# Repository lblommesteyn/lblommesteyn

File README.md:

### Hi there 👋

Welcome to My GitHub Profile! I'm glad you stopped by, my name is Luke Blommesteyn and I'm a software engineer. If you've never met me before here's some information about me:

- 🌱 I’m currently reading about the distributed systems, poker, and computer vision!
- 📫 How to reach me: lukeblommesteyn[at]gmail.com

Learn more about me [here](https://lukeblom.vercel.app)

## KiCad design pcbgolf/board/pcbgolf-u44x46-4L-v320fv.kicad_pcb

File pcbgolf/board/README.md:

# Generated boards

| file | board | layers | status |
|---|---|---|---|
| `pcbgolf-stock-2L.kicad_pcb` | 42.65 x 46.65 mm | 2 | placed + netlisted, **not routed** |

## How it is built

`tools/mkboard.py` does not synthesise footprints. It loads the upstream
`pcbgolf.kicad_pcb` — a known-valid KiCad 10 file — keeps every footprint block
verbatim, and changes only:

* the footprint's position, rotation and board side,
* pad net assignments,
* the copper stackup and the `Edge.Cuts` outline.

`tools/sexpr.py`'s serialiser is verified **lossless on all 34 upstream KiCad
files** (the PCB, 5 schematics, 28 footprints): 223,805 tokens round-trip with
zero differences. So the only new content in the output is what `mkboard.py`
deliberately writes.

## Flip convention

Placing a footprint on the back mirrors local **Y** (X unchanged), swaps
`F.*` layers for `B.*`, and sets the pad angle to `(rho - a_local) mod 360`;
on the front it is `(rho + a_local) mod 360`.

This was **derived from pcbnew itself**, not guessed: KiCad 7's
`FOOTPRINT::Flip()` and `SetOrientationDegrees()` were run on a deliberately
asymmetric test footprint and the resulting files inspected.
`tools/test_flip.py` asserts `orient_footprint()` reproduces all seven of those
ground-truth cases exactly, plus two invariants.

```
python3 tools/test_flip.py     # 9/9 pass
python3 tools/validate.py board/pcbgolf-stock-2L.kicad_pcb
```

## Validation

`validate.py` checks round-trip, layer stack, outline, every pad inside the
outline, every pad net index consistent with the net table, and that no
back-side footprint carries a stray `F.*` layer. Current result: **PASS**,
245 footprints (127 front / 118 back), 1078 pads, 196 nets, 0 pads outside.

## Not done yet

* **Routing.** Zero tracks, zero vias. The score depends on this.
* The **optimised BOM board** needs footprints that do not exist in
  `pcbgolf.pretty`: LQFP-100, SC-70-5, 0201, 0603, mid-mount USB-C, low-profile
  barrel jack, right-angle 2x4. Building it against the stock footprints fails
  validation exactly as it should — the LQFP-144 overhangs the space reserved
  for an LQFP-100 by 3.05 mm.
* **LQFP-100 pin remapping.** PF11/PG9/PG10 are not bonded out on LQFP100, so
  CH3_IMON and the FDCAN3 pair must move (FDCAN3 is also on PD12/PD13).
* **STEP export.**

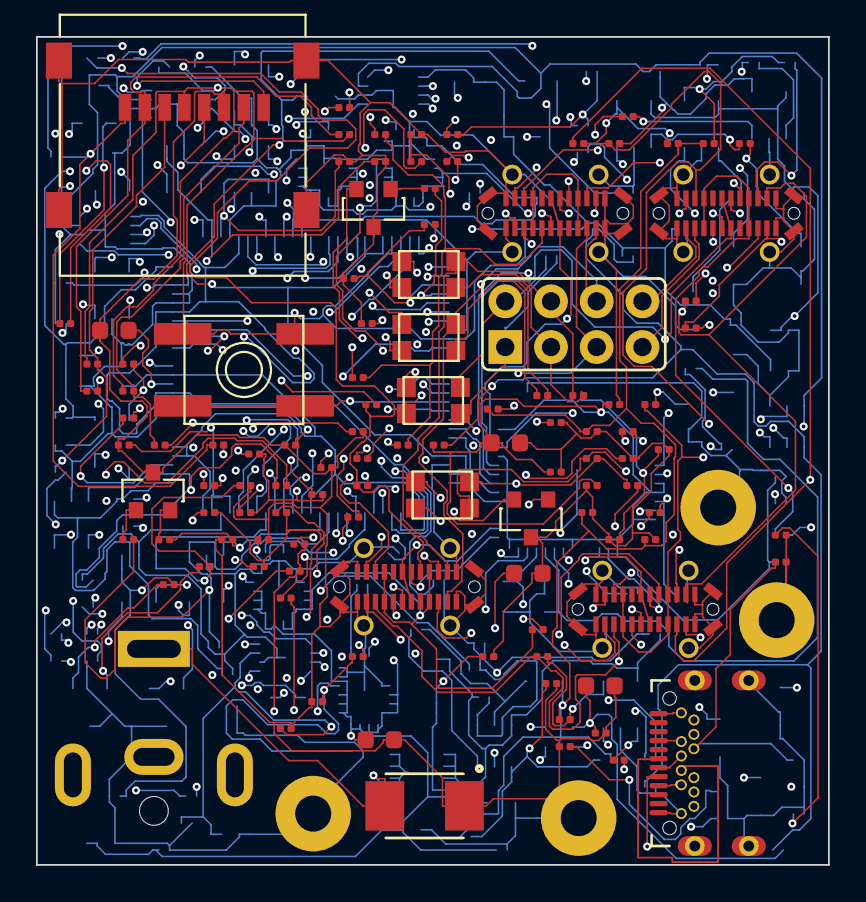
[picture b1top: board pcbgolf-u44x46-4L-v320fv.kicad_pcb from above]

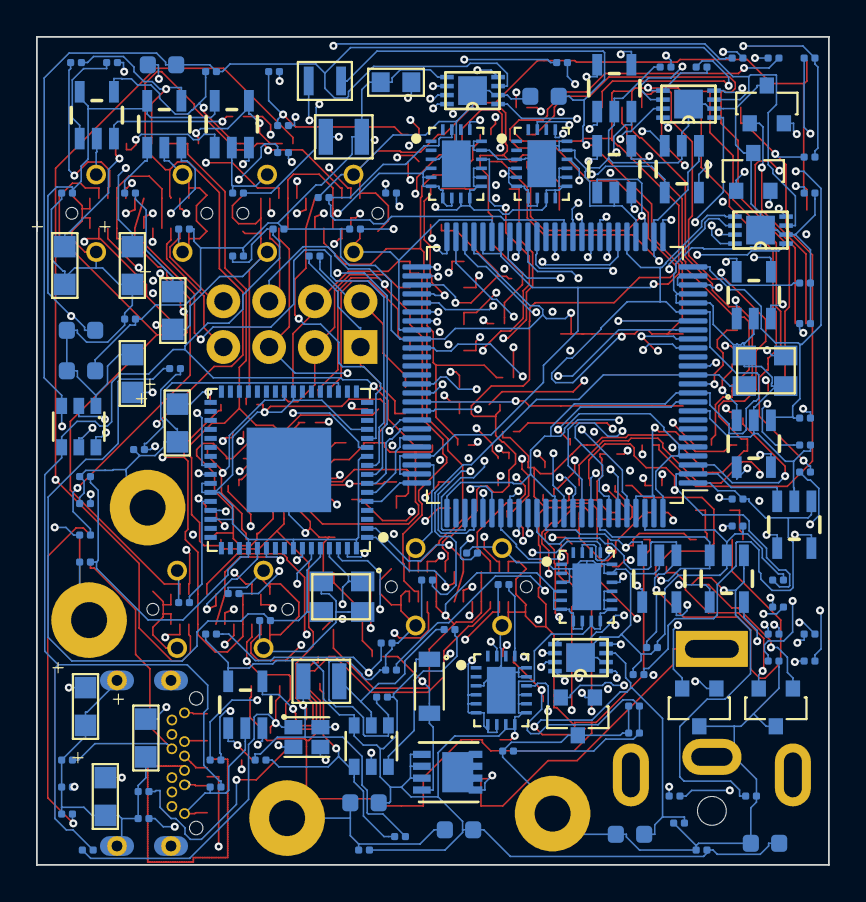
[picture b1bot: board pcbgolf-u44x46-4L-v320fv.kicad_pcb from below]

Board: 4 copper layers, 44.0 x 46.0 mm, 244 parts (129 on the bottom side), 195 nets.

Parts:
BH1, BH2, BH3, BH4: M2_BOLT
C1, C3, C8, C12, C13, C15, C19, C20, C21: 10uF; 0603-C
C2, C4, C5, C7, C9, C11, C16, C18, C22, C23, C24, C26, C27, C30, C31, C35, C36, C38, C39, C40, C41, C42, C43, C44, C45, C46, C47, C48, C49: 100nF; 0201-C
C6, C10: DNP; 0201-C
C14, C17, C28, C32: 12pF; 0201-C
C25: 220pF; 0201-C
C29, C33, C34, C37: 10u; 0201-C
C50, C51, C52, C53: 10u; 0603-C
D1: TVS-BI-DO214AA; DO-214AA(SMB)
D2: DIODEDB2W40100L; SOD-123F
J1: DCBARRELSMT; DCJACK_PJ063AH
J2: MICRO_SD-0472192001; 0472192001
J3: USB-C-FEMALE; DX07S024XJ1R1100
J4: CAN; 2X04
J5, J6, J7, J8: USB-C-FEMALEGCT; USB-C-FEMALE-VERT-GCT
L1, L2: 3u3; L-1008
L3: L-US-L2; 0603-L
L4: 2u2; 0806
L5, L6, L7, L8: ACT1210D_CHOKE; CHOKE-3.2X2.5
LED1: CREE-RGB-CLMVC
LED2: CAN0; CHIPLED
LED3: CAN1; CHIPLED
LED4: CAN2; CHIPLED
LED5: CAN3; CHIPLED
LED6, LED7, LED8, LED9: CH1_PWR; CHIPLED
LED10, LED11, LED12, LED13, LED14, LED15, LED16, LED17: LED-CC-GREEN-RED-AM23ESG; SOT23-3
Q1: SIS427-VI; PP-1212-8
Q2, Q3, Q4, Q5, Q6, Q7, Q8, Q9: NFET-DUAL-COMMON-SOURCE-QS5K2; SOT23-5
R1, R3, R7, R8, R9, R12, R28, R29, R30, R31, R32, R33, R34, R35, R36, R37, R44, R45, R50, R51, R53, R54, R56, R57, R59, R60, R78, R79, R80, R81, R98, R99, R100, R101, R102, R103, R104, R105, R122, R123, R124, R125: 10k; 0201-R
R2, R21, R23, R90, R92, R94, R96, R114, R116, R118, R120: 1k; 0201-R
R4, R5, R6, R13, R14, R15, R16, R17, R18, R19, R20, R24, R25, R52, R55, R58, R61: 100k; 0201-R
R10: 52k3; 0201-R
R22, R62, R63, R64, R65: 2k7; 0201-R
R26: 1M; 0201-R
R27: 12k; 0201-R
R38, R39, R40, R41, R42, R43: 0R; 0201-R
R46, R47, R48, R49: 60; 0201-R
R66, R67, R68, R69: 28k; 0201-R
R70, R71, R72, R73: 33k; 0201-R
R74, R75, R76, R77: 3k3; 0201-R
R82, R83, R84, R85, R86, R87, R88, R89, R91, R93, R95, R97, R106, R107, R108, R109, R110, R111, R112, R113, R115, R117, R119, R121: 100; 0201-R
SW1: SPST-2-4PIN; EVQ-Q2
U1, U2: AP62300T; SOT23-6
U3: STM32H725ZGTx; LQFP-100_14x14
U4: USB2517; QFN64-9X9
U5, U6, U7, U8: MCP2542FDT-E/MNY; TDFN8_2X3MC_MCH
U9, U10, U11, U12: OPA197IDR; SOT23-5
U13, U14, U15, U16: TPS25942; WQFN20
Y1: 25MHz; XTAL-3.2X2.5
Y2: 24MHz; XTAL-3.2X2.5

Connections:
+3V3: C6.2, C7.1, C8.1, C19.1, C20.1, C23.1, C24.1, C26.1, C27.1, C30.2, C31.2, C37.1, C42.1, C43.1, C44.1, C45.1, J2.4 (VDD), L1.2, L3.1, LED1.U1 (COM+), R4.1, R5.1, R6.1, R28.1, R29.1, R30.1, R33.1, R34.1, R35.1, R36.1, R37.1, SW1.B (S), SW1.B' (S1), U3.4, U3.5, U3.11, U3.20, U3.30, U3.47, U3.59, U3.75, U3.76, U3.88, U3.100, U4.5 (VDDA33), U4.10 (VDDA33), U4.13 (CFG_SEL2), U4.24 (VDD33CR), U4.42 (CFG_SEL1), U4.43 (RESET_N), U4.46 (VDD33), U4.52 (VDDA33), U4.57 (VDDA33), U4.64 (VDD33PLL), U5.5 (VIO), U6.5 (VIO), U7.5 (VIO), U8.5 (VIO)
+5V: C1.1, C2.1, C10.2, C11.1, C12.1, C13.1, C38.1, C39.1, C40.1, C41.1, L2.2, R1.1, R10.2, R52.2, R55.2, R58.2, R61.2, U1.3 (IN), U5.3 (VDD), U6.3 (VDD), U7.3 (VDD), U8.3 (VDD)
+12V: C3.1, C5.1, C46.1, C47.1, C48.1, C49.1, C50.1, C51.1, C52.1, C53.1, D2.1 (C), Q1.1 (S), Q1.2 (S), Q1.3 (S), R7.1, U2.3 (IN), U9.5, U10.5, U11.5, U12.5, U13.9 (VIN), U13.10 (VIN), U13.11 (VIN), U13.12 (VIN), U13.13 (VIN), U14.9 (VIN), U14.10 (VIN), U14.11 (VIN), U14.12 (VIN), U14.13 (VIN), U15.9 (VIN), U15.10 (VIN), U15.11 (VIN), U15.12 (VIN), U15.13 (VIN), U16.9 (VIN), U16.10 (VIN), U16.11 (VIN), U16.12 (VIN), U16.13 (VIN)
BTN: R12.2, SW1.A, SW1.A' (P1), U3.66, U3.94
CAN0_EN: U3.51, U5.8 (STBY)
CAN0_H: J4.2, J5.A2 (TX1+), J6.A2 (TX1+), J7.A2 (TX1+), J8.A2 (TX1+), L5.4, R46.2, R50.1
CAN0_L: J4.1, J5.A3 (TX1-), J6.A3 (TX1-), J7.A3 (TX1-), J8.A3 (TX1-), L5.3, R46.1, R51.1
CAN0_RX: U3.95, U5.4 (RXD)
CAN0_TX: U3.96, U5.1 (TXD)
CAN1_EN: U3.40, U6.8 (STBY)
CAN1_H: J4.4, J5.A11 (RX2+), J6.A11 (RX2+), J7.A11 (RX2+), J8.A11 (RX2+), L6.4, R47.2, R53.1
CAN1_L: J4.3, J5.A10 (RX2-), J6.A10 (RX2-), J7.A10 (RX2-), J8.A10 (RX2-), L6.3, R47.1, R54.1
CAN1_RX: U3.91, U6.4 (RXD)
CAN1_TX: U3.92, U6.1 (TXD)
CAN2_EN: U3.26, U7.8 (STBY)
CAN2_H: J4.6, J5.B2 (TX2+), J6.B2 (TX2+), J7.B2 (TX2+), J8.B2 (TX2+), L7.4, R48.2, R56.1
CAN2_L: J4.5, J5.B3 (TX2-), J6.B3 (TX2-), J7.B3 (TX2-), J8.B3 (TX2-), L7.3, R48.1, R57.1
CAN2_RX: U3.56, U7.4 (RXD)
CAN2_TX: U3.57, U7.1 (TXD)
CAN3_EN: U3.78, U8.8 (STBY)
CAN3_H: J4.8, J5.B11 (RX1+), J6.B11 (RX1+), J7.B11 (RX1+), J8.B11 (RX1+), L8.4, R49.2, R59.1
CAN3_L: J4.7, J5.B10 (RX1-), J6.B10 (RX1-), J7.B10 (RX1-), J8.B10 (RX1-), L8.3, R49.1, R60.1
CAN3_RX: U3.48, U8.4 (RXD)
CAN3_TX: U3.49, U8.1 (TXD)
CH1_D_N: J5.A7 (D-A), J5.B7 (D-B), U4.53 (USBDN6_DM)
CH1_D_P: J5.A6 (D+A), J5.B6 (D+B), U4.54 (USBDN6_DP)
CH1_IMON: R70.2, U3.34, U13.19 (IMON)
CH1_PWR_EN: U3.41, U13.14 (EN)
CH1_SBU1: J5.A8 (SBU1), R19.2, R90.2, R91.2
CH1_SBU1_IGN: Q2.1 (G1), R78.1, R83.2, U3.85
CH1_SBU1_RELAY: Q2.3 (G2), R82.2, R98.2, U3.93
CH1_SBU2: J5.B8 (SBU2), R20.2, R114.2, R115.2
CH1_SBU2_IGN: Q6.1 (G1), R102.1, R107.2, U3.1
CH1_SBU2_RELAY: Q6.3 (G2), R106.2, R122.2, U3.2
CH2_D_N: J6.A7 (D-A), J6.B7 (D-B), U4.11 (USBDN5_DM)
CH2_D_P: J6.A6 (D+A), J6.B6 (D+B), U4.12 (USBDN5_DP)
CH2_IMON: R71.2, U3.37, U14.19 (IMON)
CH2_PWR_EN: U3.52, U14.14 (EN)
CH2_SBU1: J6.A8 (SBU1), R15.2, R92.2, R93.2
CH2_SBU1_IGN: Q3.1 (G1), R79.1, R85.2, U3.25
CH2_SBU1_RELAY: Q3.3 (G2), R84.2, R99.2, U3.60
CH2_SBU2: J6.B8 (SBU2), R13.2, R116.2, R117.2
CH2_SBU2_IGN: Q7.1 (G1), R103.1, R109.2, U3.55
CH2_SBU2_RELAY: Q7.3 (G2), R108.2, R123.2, U3.3
CH3_D_N: J7.A7 (D-A), J7.B7 (D-B), U4.8 (USBDN4_DM)
CH3_D_P: J7.A6 (D+A), J7.B6 (D+B), U4.9 (USBDN4_DP)
CH3_IMON: R72.2, U3.31, U15.19 (IMON)
CH3_PWR_EN: U3.68, U15.14 (EN)
CH3_SBU1: J7.A8 (SBU1), R17.2, R94.2, R95.2
CH3_SBU1_IGN: Q4.1 (G1), R80.1, R87.2, U3.86
CH3_SBU1_RELAY: Q4.3 (G2), R86.2, R100.2, U3.87
CH3_SBU2: J7.B8 (SBU2), R18.2, R118.2, R119.2
CH3_SBU2_IGN: Q8.1 (G1), R104.1, R111.2, U3.54
CH3_SBU2_RELAY: Q8.3 (G2), R110.2, R124.2, U3.53
CH4_D_N: J8.A7 (D-A), J8.B7 (D-B), U4.1 (USBDN1_DM)
CH4_D_P: J8.A6 (D+A), J8.B6 (D+B), U4.2 (USBDN1_DP)
CH4_IMON: R73.2, U3.16, U16.19 (IMON)
CH4_PWR_EN: U3.83, U16.14 (EN)
CH4_SBU1: J8.A8 (SBU1), R16.2, R96.2, R97.2
CH4_SBU1_IGN: Q5.1 (G1), R81.1, R89.2, U3.28
CH4_SBU1_RELAY: Q5.3 (G2), R88.2, R101.2, U3.67
CH4_SBU2: J8.B8 (SBU2), R14.2, R120.2, R121.2
CH4_SBU2_IGN: Q9.1 (G1), R105.1, R113.2, U3.27
CH4_SBU2_RELAY: Q9.3 (G2), R112.2, R125.2, U3.50
GND: BH1.0 (1_0), BH2.0 (1_0), BH3.0 (1_0), BH4.0 (1_0), C1.2, C2.2, C3.2, C5.2, C7.2, C8.2, C11.2, C12.2, C13.2, C14.2, C15.2, C16.2, C17.2, C18.2, C19.2, C20.2, C21.2, C22.2, C23.2, C24.2, C25.2, C26.2, C27.2, C28.2, C29.2, C30.1, C31.1, C32.2, C33.2, C34.2, C35.1, C36.1, C37.2, C38.2, C39.2, C40.2, C41.2, C42.2, C43.2, C44.2, C45.2, C46.2, C47.2, C48.2, C49.2, C50.2, C51.2, C52.2, C53.2, D1.1, J1.2, J2.6 (VSS), J2.G1 (GND), J2.G2 (GND), J2.G3 (GND), J2.G4 (GND), J3.A1 (GND), J3.A12 (GND), J3.B1 (GND), J3.B1T (GND), J3.B12 (GND), J3.B12T (GND), J3.S1B (SHIELDA), J3.S1T (SHIELDA), J3.S1TH (SHIELDA), J3.S2B (SHIELDA), J3.S2T (SHIELDA), J3.S2TH (SHIELDA), J3.S3B (SHIELDB), J3.S3T (SHIELDB), J3.S3TH (SHIELDB), J3.S4B (SHIELDB), J3.S4T (SHIELDB), J3.S4TH (SHIELDB), J5.A1 (GND), J5.A12 (GND), J5.B1 (GND), J5.B12 (GND), J5.S1 (SHIELDA), J5.S2 (SHIELDA), J5.S3 (SHIELDA), J5.S4 (SHIELDA), J5.S11 (SHIELDB), J5.S12 (SHIELDB), J5.S13 (SHIELDB), J5.S14 (SHIELDB), J6.A1 (GND), J6.A12 (GND), J6.B1 (GND), J6.B12 (GND), J6.S1 (SHIELDA), J6.S2 (SHIELDA), J6.S3 (SHIELDA), J6.S4 (SHIELDA), J6.S11 (SHIELDB), J6.S12 (SHIELDB), J6.S13 (SHIELDB), J6.S14 (SHIELDB), J7.A1 (GND), J7.A12 (GND), J7.B1 (GND), J7.B12 (GND), J7.S1 (SHIELDA), J7.S2 (SHIELDA), J7.S3 (SHIELDA), J7.S4 (SHIELDA), J7.S11 (SHIELDB), J7.S12 (SHIELDB), J7.S13 (SHIELDB), J7.S14 (SHIELDB), J8.A1 (GND), J8.A12 (GND), J8.B1 (GND), J8.B12 (GND), J8.S1 (SHIELDA), J8.S2 (SHIELDA), J8.S3 (SHIELDA), J8.S4 (SHIELDA), J8.S11 (SHIELDB), J8.S12 (SHIELDB), J8.S13 (SHIELDB), J8.S14 (SHIELDB), LED2.C, LED3.C, LED4.C, LED5.C, LED6.C, LED7.C, LED8.C, LED9.C, LED10.3 (C), LED11.3 (C), LED12.3 (C), LED13.3 (C), LED14.3 (C), LED15.3 (C), LED16.3 (C), LED17.3 (C), Q2.2 (S), Q3.2 (S), Q4.2 (S), Q5.2 (S), Q6.2 (S), Q7.2 (S), Q8.2 (S), Q9.2 (S), R2.1, R3.2, R8.2, R9.2, R12.1, R25.1, R27.1, R31.2, R32.2, R44.2, R45.2, R66.1, R67.1, R68.1, R69.1, R70.1, R71.1, R72.1, R73.1, R78.2, R79.2, R80.2, R81.2, R98.1, R99.1, R100.1, R101.1, R102.2, R103.2, R104.2, R105.2, R122.1, R123.1, R124.1, R125.1, U1.1 (GND), U2.1 (GND), U3.9, U3.21, U3.22, U3.29, U3.45, U3.58, U3.73, U3.98, U4.19 (TEST), U4.PAD (VSS), U5.2 (VSS), U5.PAD (EPAD), U6.2 (VSS), U6.PAD (EPAD), U7.2 (VSS), U7.PAD (EPAD), U8.2 (VSS), U8.PAD (EPAD), U9.2, U10.2, U11.2, U12.2, U13.3 (PGTH), U13.15 (OVP), U13.16 (GND), U13.PAD (GND), U14.3 (PGTH), U14.15 (OVP), U14.16 (GND), U14.PAD (GND), U15.3 (PGTH), U15.15 (OVP), U15.16 (GND), U15.PAD (GND), U16.3 (PGTH), U16.15 (OVP), U16.16 (GND), U16.PAD (GND), Y1.2 (3), Y1.4 (3), Y2.2 (3), Y2.4 (3)
HUB_SCL: R30.2, U3.42, U4.41 (SCL)
HUB_SDA: R28.2, U3.43, U4.40 (SDA)
LED_B: R23.2, U3.89
LED_G: R22.2, U3.82
LED_R: R21.2, U3.90
unnamed: D1.2, J1.1, Q1.5 (D), Q1.6 (D), Q1.7 (D), Q1.8 (D), Q1.9 (D)
unnamed: C9.1, U2.6 (BST)
unnamed: C9.2, L2.1, U2.2 (SW)
unnamed: R1.2, U1.5 (EN)
unnamed: C4.2, L1.1, U1.2 (SW)
unnamed: C6.1, R3.1, R4.2, R5.2, R6.2, U1.4 (FB)
unnamed: C4.1, U1.6 (BST)
unnamed: D2.2 (A), Q1.4 (G), R2.2
unnamed: R7.2, R8.1, U2.5 (EN)
unnamed: C10.1, R9.1, R10.1, U2.4 (FB)
unnamed: LED1.U2 (R-), R21.1
unnamed: LED1.U3 (G-), R22.1
unnamed: LED1.U4 (B-), R23.1
unnamed: C14.1, U3.13, Y1.1
unnamed: R13.1, U3.32
unnamed: R14.1, U3.36
unnamed: R15.1, U3.19
unnamed: R16.1, U3.33
unnamed: C17.1, U3.14, Y1.3 (2)
unnamed: R17.1, U3.38
unnamed: R18.1, U3.35
unnamed: R19.1, U3.17
unnamed: R20.1, U3.18
unnamed: C33.1, C35.2, U4.25 (VDD18)
unnamed: R24.1, R25.2, U4.44 (VBUS_DET)
unnamed: R29.2, U4.45 (SUSP_IND)
unnamed: C32.1, R26.1, U4.60 (XTAL2), Y2.3 (2)
unnamed: C28.1, R26.2, U4.61 (XTAL1), Y2.1
unnamed: C34.1, C36.2, U4.62 (VDD18PLL)
unnamed: R27.2, U4.63 (RBIAS)
unnamed: J3.A5 (CC1), R31.1, R32.1
unnamed: J3.B2 (TX2+), J3.B2T (TX2+)
unnamed: J3.B3 (TX2-), J3.B3T (TX2-)
unnamed: J3.B5 (CC2), J3.B5T (CC2), R44.1, R45.1
unnamed: J3.B8 (SBU2), J3.B8T (SBU2)
unnamed: J3.B10 (RX1-), J3.B10T (RX1-)
unnamed: J3.B11 (RX1+), J3.B11T (RX1+)
unnamed: J2.7 (DAT0), R33.2, R38.2
unnamed: J2.8 (DAT1), R34.2, R39.2
unnamed: J2.2 (CD/DAT3), R36.2, R41.2
unnamed: J2.3 (CMD), R37.2, R42.2
unnamed: J2.1 (DAT2), R35.2, R40.2
unnamed: J2.5 (CLK), R43.2
unnamed: R64.1, U11.1
unnamed: LED4.A, R64.2
unnamed: R50.2, U9.3
unnamed: R51.2, R52.1, U9.4
unnamed: R62.1, U9.1
unnamed: LED2.A, R62.2
unnamed: R57.2, R58.1, U11.4
unnamed: LED3.A, R63.2
unnamed: R56.2, U11.3
unnamed: LED5.A, R65.2
unnamed: L8.1, U8.7 (CANH)
unnamed: L8.2, U8.6 (CANL)
unnamed: R65.1, U12.1
unnamed: R53.2, U10.3
unnamed: R54.2, R55.1, U10.4
unnamed: R63.1, U10.1
unnamed: R59.2, U12.3
unnamed: L7.2, U7.6 (CANL)
unnamed: L7.1, U7.7 (CANH)
unnamed: L5.2, U5.6 (CANL)
unnamed: L5.1, U5.7 (CANH)
unnamed: R60.2, R61.1, U12.4
unnamed: L6.2, U6.6 (CANL)
unnamed: L6.1, U6.7 (CANH)
unnamed: J7.A4 (VBUS), J7.A9 (VBUS), J7.B4 (VBUS), J7.B9 (VBUS), R76.1, U15.4 (VOUT), U15.5 (VOUT), U15.6 (VOUT), U15.7 (VOUT), U15.8 (VOUT)
unnamed: Q2.4 (D2), R91.1
unnamed: Q2.5 (D1), R90.1
unnamed: Q3.4 (D2), R93.1
unnamed: J5.A4 (VBUS), J5.A9 (VBUS), J5.B4 (VBUS), J5.B9 (VBUS), R74.1, U13.4 (VOUT), U13.5 (VOUT), U13.6 (VOUT), U13.7 (VOUT), U13.8 (VOUT)
unnamed: R66.2, U13.17 (ILIM)
unnamed: J6.A4 (VBUS), J6.A9 (VBUS), J6.B4 (VBUS), J6.B9 (VBUS), R75.1, U14.4 (VOUT), U14.5 (VOUT), U14.6 (VOUT), U14.7 (VOUT), U14.8 (VOUT)
unnamed: R67.2, U14.17 (ILIM)
unnamed: R68.2, U15.17 (ILIM)
unnamed: Q5.5 (D1), R96.1
unnamed: Q9.4 (D2), R121.1
unnamed: Q9.5 (D1), R120.1
unnamed: J8.A4 (VBUS), J8.A9 (VBUS), J8.B4 (VBUS), J8.B9 (VBUS), R77.1, U16.4 (VOUT), U16.5 (VOUT), U16.6 (VOUT), U16.7 (VOUT), U16.8 (VOUT)
unnamed: LED9.A, R77.2
unnamed: LED14.1 (AR), R107.1
unnamed: LED14.2 (AG), R106.1
unnamed: LED15.1 (AR), R109.1
unnamed: LED15.2 (AG), R108.1
unnamed: Q7.4 (D2), R117.1
unnamed: Q7.5 (D1), R116.1
unnamed: LED8.A, R76.2
unnamed: LED7.A, R75.2
unnamed: LED16.2 (AG), R110.1
unnamed: LED11.1 (AR), R85.1
unnamed: LED11.2 (AG), R84.1
unnamed: Q6.4 (D2), R115.1
unnamed: LED17.2 (AG), R112.1
unnamed: Q6.5 (D1), R114.1
unnamed: R69.2, U16.17 (ILIM)
unnamed: LED13.1 (AR), R89.1
unnamed: Q8.4 (D2), R119.1
unnamed: Q8.5 (D1), R118.1
unnamed: LED6.A, R74.2
unnamed: LED16.1 (AR), R111.1
unnamed: LED10.1 (AR), R83.1
unnamed: LED10.2 (AG), R82.1
unnamed: Q5.4 (D2), R97.1
unnamed: Q4.5 (D1), R94.1
unnamed: LED17.1 (AR), R113.1
unnamed: LED13.2 (AG), R88.1
unnamed: Q4.4 (D2), R95.1
unnamed: LED12.1 (AR), R87.1
unnamed: LED12.2 (AG), R86.1
unnamed: Q3.5 (D1), R92.1
SD_CLK: R43.1, U3.81
SD_CMD: R42.1, U3.84
SD_D0: R38.1, U3.64
SD_D1: R39.1, U3.65
SD_D2: R40.1, U3.79
SD_D3: R41.1, U3.80
STM_D_N: U3.69, U4.7 (USBDN3_DP)
STM_D_P: U3.70, U4.6 (USBDN3_DM)
USB_D_N: J3.A7 (D-A), J3.B7 (D-B), J3.B7T (D-B), U4.59 (USBUP_DP)
USB_D_P: J3.A6 (D+A), J3.B6 (D+B), J3.B6T (D+B), U4.58 (USBUP_DM)
VBUS: C29.1, J3.A4 (VBUS), J3.A9 (VBUS), J3.B4 (VBUS), J3.B4T (VBUS), J3.B9 (VBUS), J3.B9T (VBUS), R24.2
VDDA: C22.1, L3.2, U3.23, U3.24
VDDLDO: C15.1, C16.1, C18.1, C21.1, L4.1, U3.12, U3.44, U3.46, U3.72, U3.74, U3.97, U3.99
VLXSMPS: C25.1, L4.2, U3.10

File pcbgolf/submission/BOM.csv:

qty,refs,value,orig_footprint,orig_mpn,new_footprint,new_part,risk,rationale
42,R1 R100 R101 R102 R103 R104 R105 R12 R122 R123 R124 R125 R28 R29 R3 R30 R31 R32 R33 R34 R35 R36 R37 R44 R45 R50 R51 R53 R54 R56 R57 R59 R60 R7 R78 R79 R8 R80 R81 R9 R98 R99,10k,0402-R,RC0402FR-0710KL,0201-R,0201 thick-film,low,JLCPCB assembles 0201; all resistor values available
29,C11 C16 C18 C2 C22 C23 C24 C26 C27 C30 C31 C35 C36 C38 C39 C4 C40 C41 C42 C43 C44 C45 C46 C47 C48 C49 C5 C7 C9,100nF,0402-C,CL05F104ZO5NNNC,0201-C,0201 X5R/X7R,low,100nF/12pF/220pF fine in 0201; keep 10uF at 0402
24,R106 R107 R108 R109 R110 R111 R112 R113 R115 R117 R119 R121 R82 R83 R84 R85 R86 R87 R88 R89 R91 R93 R95 R97,100,0402-R,RC0402JR-07100RL,0201-R,0201 thick-film,low,JLCPCB assembles 0201; all resistor values available
17,R13 R14 R15 R16 R17 R18 R19 R20 R24 R25 R4 R5 R52 R55 R58 R6 R61,100k,0402-R,RC0402JR-07100KL,0201-R,0201 thick-film,low,JLCPCB assembles 0201; all resistor values available
11,R114 R116 R118 R120 R2 R21 R23 R90 R92 R94 R96,1k,0402-R,RC0402JR-071KL,0201-R,0201 thick-film,low,JLCPCB assembles 0201; all resistor values available
9,C1 C12 C13 C15 C19 C20 C21 C3 C8,10uF,0805-C,CL21A106KAYNNNE,0603-C,0603 10uF 25V X5R,low,10uF 0603 widely stocked; derate check on 12V rail
8,LED10 LED11 LED12 LED13 LED14 LED15 LED16 LED17,LED-CC-GREEN-RED-AM23ESG,SOT23-3,AM23ESGW,SOT23-3,(unchanged),-,
8,Q2 Q3 Q4 Q5 Q6 Q7 Q8 Q9,NFET-DUAL-COMMON-SOURCE-QS5K2,SOT23-5,QS5K2TR,SOT23-5,(unchanged),-,
6,R38 R39 R40 R41 R42 R43,0R,0402-R,RMCF0402ZT0R00,0201-R,0201 thick-film,low,JLCPCB assembles 0201; all resistor values available
5,R22 R62 R63 R64 R65,2k7,0402-R,RC0402JR-072K7L,0201-R,0201 thick-film,low,JLCPCB assembles 0201; all resistor values available
4,C14 C17 C28 C32,12pF,0402-C,C0402C120J5GACTU,0201-C,0201 X5R/X7R,low,100nF/12pF/220pF fine in 0201; keep 10uF at 0402
4,C29 C33 C34 C37,10u,0402-C,GRM155R61A106ME11D,0201-C,0201 X5R/X7R,low,100nF/12pF/220pF fine in 0201; keep 10uF at 0402
4,R70 R71 R72 R73,33k,0402-R,RC0402JR-0733KL,0201-R,0201 thick-film,low,JLCPCB assembles 0201; all resistor values available
4,R74 R75 R76 R77,3k3,0402-R,RC0402JR-073K3L,0201-R,0201 thick-film,low,JLCPCB assembles 0201; all resistor values available
4,R66 R67 R68 R69,28k,0402-R,RK73H1ETTP2802F,0201-R,0201 thick-film,low,JLCPCB assembles 0201; all resistor values available
4,R46 R47 R48 R49,60,0402-R,RC0402FR-0760R4L,0201-R,0201 thick-film,low,JLCPCB assembles 0201; all resistor values available
4,C50 C51 C52 C53,10u,0805-C,CL21A106KAYNNNE,0603-C,0603 10uF 25V X5R,low,10uF 0603 widely stocked; derate check on 12V rail
4,LED6 LED7 LED8 LED9,CH1_PWR,CHIPLED,LG R971-KN-1,CHIPLED,(unchanged),-,
4,L5 L6 L7 L8,ACT1210D_CHOKE,CHOKE-3.2X2.5,ACT1210D-101-2P-TL00,CHOKE-3.2X2.5,(unchanged),-,
4,BH1 BH2 BH3 BH4,M2_BOLT,M2_BOLT,,M2_BOLT,(unchanged),-,
4,U10 U11 U12 U9,OPA197IDR,SOIC-8_3.9x4.9mm_P1.27mm,OPA197IDR,SOT23-5,OPA197IDBVR,none,"same OPA197 die and 36V rating as the specified OPA197IDR, in SOT-23-5 instead of SOIC-8: 12 mm^2 instead of 40."
4,U5 U6 U7 U8,MCP2542FDT-E/MNY,TDFN8_2X3MC_MCH,MCP2542FDT-H/MNY,TDFN8_2X3MC_MCH,(unchanged),-,
4,J5 J6 J7 J8,USB-C-FEMALEGCT,USB-C-FEMALE-VERT-GCT,10132328-10011LF,USB-C-FEMALE-VERT-GCT,(unchanged),-,
4,U13 U14 U15 U16,TPS25942,WQFN20,TPS25944ARVCR,WQFN20,(unchanged),-,
2,C10 C6,DNP,0402-C,,0201-C,0201 X5R/X7R,low,100nF/12pF/220pF fine in 0201; keep 10uF at 0402
2,L1 L2,3u3,L-1008,MEKK2520T3R3M,L-1008,(unchanged),-,
2,U1 U2,AP62300T,SOT23-6,AP62300WU-7,SOT23-6,(unchanged),-,
1,C25,220pF,0402-C,04025A221FAT2A,0201-C,0201 X5R/X7R,low,100nF/12pF/220pF fine in 0201; keep 10uF at 0402
1,R27,12k,0402-R,CRGCQ0402F12K,0201-R,0201 thick-film,low,JLCPCB assembles 0201; all resistor values available
1,R26,1M,0402-R,RC0402JR-071ML,0201-R,0201 thick-film,low,JLCPCB assembles 0201; all resistor values available
1,R10,52k3,0402-R,RC0402FR-0752K3L,0201-R,0201 thick-film,low,JLCPCB assembles 0201; all resistor values available
1,J2,MICRO_SD-0472192001,0472192001,47219-2001,0472192001,(unchanged),-,
1,L3,L-US-L2,0603-L,MH1608-601Y,0603-L,(unchanged),-,
1,L4,2u2,0806,LQM2MPN2R2NG0L,0806,(unchanged),-,
1,J4,CAN,2X04,,2X04,(unchanged),-,
1,LED2,CAN0,CHIPLED,LG R971-KN-1,CHIPLED,(unchanged),-,
1,LED4,CAN2,CHIPLED,LG R971-KN-1,CHIPLED,(unchanged),-,
1,LED3,CAN1,CHIPLED,LG R971-KN-1,CHIPLED,(unchanged),-,
1,LED5,CAN3,CHIPLED,LG R971-KN-1,CHIPLED,(unchanged),-,
1,LED1,CREE-RGB-CLMVC,CREE-RGB-CLMVC,CLMVC-FKA-CL1D1L71BB7C3C3,CREE-RGB-CLMVC,(unchanged),-,
1,J1,DCBARRELSMT,DCJACK_2MM_SMT,PJ-002AH-SMT-TR,DCJACK_PJ063AH,"CUI PJ-063AH (2.0mm pin, 5.5mm OD, 24V 8A, through-hole)",low,same 5.5/2.0mm plug; 2mm lower; pins 3.0mm below the top face
1,D1,TVS-BI-DO214AA,DO-214AA(SMB),SMAJ16CA-13-F,DO-214AA(SMB),(unchanged),-,
1,J3,USB-C-FEMALE,DX07S024XJ1R1100,DX07S024XJ1R1100,DX07S024XJ1R1100,(unchanged),-,
1,SW1,SPST-2-4PIN,EVQ-Q2,EVQ-Q2Y03W,EVQ-Q2,(unchanged),-,
1,U3,STM32H725ZGTx,LQFP-144_20x20mm_P0.5mm,STM32H725ZGT,LQFP-100_14x14,STM32H725VGT6,low,"same die/flash, 82 GPIO vs 50 needed; no escape vias"
1,Q1,SIS427-VI,PP-1212-8,SI7101DN-T1-GE3,PP-1212-8,(unchanged),-,
1,U4,USB2517,QFN64-9X9,USB2517,QFN64-9X9,(unchanged),-,
1,D2,DIODEDB2W40100L,SOD-123F,PMEG10020ELRX,SOD-123F,(unchanged),-,
1,Y2,24MHz,XTAL-3.2X2.5,ABM8AIG-24.000MHZ-12-2Z-T3,XTAL-3.2X2.5,(unchanged),-,
1,Y1,25MHz,XTAL-3.2X2.5,RH100-25.000-12-F-1010-TR,XTAL-3.2X2.5,(unchanged),-,

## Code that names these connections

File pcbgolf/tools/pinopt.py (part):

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          'N$29', 'N$30', 'N$31', 'N$32', 'N$35', 'N$36', 'N$37', 'N$38']
GPIO_DRIVE = ([f'CH{i}_PWR_EN' for i in range(1, 5)] +
              [f'CH{i}_SBU{j}_{k}' for i in range(1, 5) for j in (1, 2) for k in ('IGN', 'RELAY')])
GPIO_SAFE = ['CAN0_EN', 'CAN1_EN', 'CAN2_EN', 'CAN3_EN', 'LED_R', 'LED_G', 'LED_B', 'BTN']
ADC_PINS = {'PA0', 'PA1', 'PA2', 'PA3', 'PA4', 'PA5', 'PA6', 'PA7', 'PB0', 'PB1',
            'PC0', 'PC1', 'PC2_C', 'PC3_C', 'PC4', 'PC5'}
ANALOG_ONLY = {'PC2_C', 'PC3_C'}
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    used_fixed = {pin_name(n) for n, net in remap.items() if net not in signals}
    pool = [n for n in PINS if re.match(r'^P[A-E]\d+', pin_name(n))
            and pin_name(n) not in RESERVED and pin_name(n) not in used_fixed]
    # BOOT0 shares the BTN net; keep it, and steer the BTN GPIO toward it
    targets = {}
    for s in signals:
        pts = [pos[p] for p in bynet[s] if p[0] != 'U3']
        if s == 'BTN':
            pts += [pos[('U3', n)] for n in remap if remap[n] == 'BTN' and pin_name(n) == 'BOOT0']
        targets[s] = centroid(pts)
    INF = 1e6
    C = np.zeros((len(signals), len(pool)))
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
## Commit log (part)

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2025-12-25 Update 3D profile contribution graph
2026-05-12 Revise introduction and work experience in README
    Updated personal introduction and work experience.
